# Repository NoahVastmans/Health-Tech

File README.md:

# 🎾 SmartServe Ball — Intelligent Motion Guidance and Apex Detection

## 📘 Project Overview

The **SmartServe Ball** project combines embedded sensing, wireless communication, and data analysis to accurately detect and predict the **apex** of a tennis ball’s trajectory during a throw or serve.

Using a **Seeed XIAO BLE Sense** microcontroller with a **6-axis IMU (LSM6DS3)**, the system identifies:
- The **start of free fall**
- The **apex (highest point)** of the throw
- The **catch or impact moment**
- And transmits timing data via **Bluetooth Low Energy (BLE)**

The goal is to provide **real-time motion insight** for sports technology, validation through **video tracking**, and a foundation for further embedded motion analytics.

---

## 📁 Repository Structure

### 🧠 `Arduino Scripts/`
Contains all embedded code for the SmartServe Ball, including:
- **Apex detection**, **free-fall**, and **BLE telemetry algorithms**
- Modified **`LSM6DS3.cpp`** file required for stable IMU communication  
  *(instructions are detailed in the script-specific README inside this folder)*

Each Arduino script is fully documented in-code.

---

### ⚡ `Electrical Circuit/`
Includes the electrical design and assembly details:
- **KiCad project files** for the wiring and sensor connections  
- **Photos** of the final sensor assembly

> 💡 The PCB was **not fully designed** in CAD — instead, an **adaptable PCB prototyping board** was used.  
> This allowed greater flexibility for multi-layer connections and double-sided component placement.

---

### 🧱 `Prototype Sensor Case/`
3D design files for the **protective casing** used to house the electronics inside a **tennis ball**.  
The case ensures durability while maintaining balance and minimal aerodynamic impact.

---

### 🎥 `Video Tracking/`
Contains:
- The **validation videos** used to visually confirm the apex timing  
- **Video tracking scripts** for extracting apex frames and timestamps  
- A **comparison file** matching BLE-detected and predicted times to the visual apex times

This folder provides the link between **experimental results** and **sensor-based detection accuracy**.

---

### 📹 `Explanation Video/`
A short **demonstration video** summarizing the SmartServe Ball project — explaining the concept and system design in a clear visual format.

---

### 🖥️ `Presentation/`
Contains the **final project presentation slides**, summarizing:
- Motivation and goals  
- Technical design (hardware + software)  
- Validation results and future improvements  

---

### 📄 `Scientific Paper/`
Includes a **concise research-style paper** presenting:
- The experimental setup  
- Measured results  
- Comparison between prediction and detection  
- Relevant literature and references  

---

### 🕰️ `Legacy/`
Contains earlier versions of scripts and design assets intended for future development.  
A separate README inside this folder explains each file’s purpose and how to build upon it.

---

## 🧩 Summary

| Component | Description |
|------------|--------------|
| **Embedded Code** | Apex detection, prediction, BLE telemetry |
| **Electronics** | IMU wiring and modular circuit design |
| **Mechanical Design** | 3D CAD for protective case |
| **Validation** | Video-based apex verification |
| **Demonstration** | Project explanation video |
| **Documentation** | Presentation slides and scientific paper |
| **Legacy Work** | Early-stage materials for continuation |

---

## 🔬 Purpose

The SmartServe Ball demonstrates how **low-power embedded sensing** and **motion algorithms** can yield **accurate trajectory analytics** for sports applications.  
It combines open hardware, transparent validation, and modular design to serve as a **research and development platform** for motion-based performance tracking.

---

## 🧾 License

This repository is open for **educational and research use**.  
Please credit the **SmartServe Ball Project** when reusing or modifying any material.

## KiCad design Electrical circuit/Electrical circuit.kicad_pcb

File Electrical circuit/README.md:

# ⚡ SmartServe Ball — Electrical Circuit

## 📘 Overview

This folder contains all **electrical design resources** for the SmartServe Ball project.  
The system connects a **Seeed XIAO BLE Sense** microcontroller to a **buzzer** and other peripheral components.

---

## 🧩 Contents

| Item | Description |
|------|--------------|
| `SmartServeBall.kicad_sch` | Main circuit schematic showing all connections between the XIAO BLE Sense, IMU, and buzzer |
| `SmartServeBall.kicad_pro` | KiCad project configuration file |
| `Seeeduino XIAO KICAD/` | KiCad symbol and footprint files for Seeed components (used in the schematic) |
| `Assembly Photos/` | Images of the final sensor assembly and adaptable PCB setup |

---

## 🧠 Design Notes

- Only the **schematic** was designed digitally in KiCad.  
- The **PCB itself was not routed** in KiCad or fabricated.

Instead, an **adaptable prototyping PCB** was used for greater flexibility:
- Components were mounted on **both sides** of the board.  
- Components were mounted on top of each other to save space.  
- This approach allowed **rapid iteration** and **easy modification** during testing and validation.

---

## 🔌 Connection Overview

The schematic illustrates: 
- **Power lines** (`3.3V` and `GND`) shared between all components  
- **Digital output pin (D5)** used to drive the **buzzer** for apex and event feedback

---

## 🧰 Tools

- **KiCad 7.x or later** (for viewing and editing schematic files)  
- **Seeeduino XIAO KICAD Library** (included in this folder)

To open the schematic correctly:
1. Ensure the `Seeeduino XIAO KICAD/` folder is in the same directory as the `.kicad_pro` file.  
2. Open `SmartServeBall.kicad_pro` in KiCad.  
3. Verify that component symbols and footprints load without errors.

---

## 🧱 Assembly Process

The assembly was performed in several structured steps to create a compact and robust sensor module:

1. **Top Layer Soldering:**  
   The first layer of components was soldered on the **upper side** of the adaptable PCB.  
   This included the **buzzer**, **resistor**, and **pin extensions** for the Seeed XIAO BLE Sense.

2. **Power Wiring:**  
   Next, the **power supply wires** were soldered to the corresponding **3.3V** and **GND** pins, ensuring solid electrical contact and mechanical stability.

3. **Base Layer Protection:**  
   After soldering the lower connections, a **thin layer of hot glue** was applied to the **bottom side** of the PCB to insulate and protect the solder joints.

4. **Battery Holder Placement:**  
   The **battery holder** was then positioned directly on top of the glued surface, forming the **second hardware layer** of the design.

5. **Final Power Connection:**  
   Finally, the **power wires** were soldered to the **battery holder terminals**, completing the electrical circuit and enabling portable operation.

This stacked-layer assembly provided an **efficient use of space** and **robust wiring**, allowing the electronics to fit neatly inside the SmartServe Ball’s protective enclosure.

---

## 📷 Assembly

The `Assembly_Photos/` folder shows:
- The **adaptable PCB layout**  
- The **component placement** on both board sides  

These images serve as a **reference for replication or redesign**.

---

## 🧾 License

These files are shared for **educational and research purposes** under the SmartServe Ball project.  
Please credit the **SmartServe Ball Team** when reusing or adapting the schematic or library components.

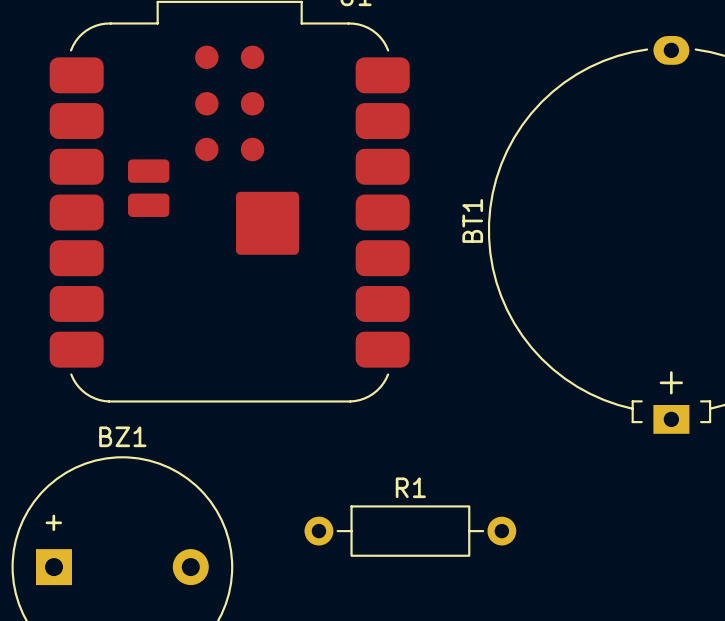
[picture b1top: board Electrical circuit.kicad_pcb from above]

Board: 2 copper layers, 4 parts (0 on the bottom side), 4 nets, no tracks yet.

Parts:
BT1: Battery_Cell; Battery_Panasonic_CR2032-HFN_Horizontal_CircularHoles
BZ1: Buzzer; Buzzer_12x9.5RM7.6
R1: 33 Ohm; R_Axial_DIN0207_L6.3mm_D2.5mm_P10.16mm_Horizontal
U1: SeeeduinoXIAO; MCU_Seeed_ESP32C3

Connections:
GND: BT1.2 (-), R1.2, U1.13 (GND)
unnamed: BT1.1 (+), U1.12 (3V3)
unnamed: BZ1.1 (+), U1.5 (PA8_A4_D4_SDA)
unnamed: BZ1.2 (-), R1.1

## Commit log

2025-09-10 Attempt to store data on flash memory
2025-09-17 Create FindingVelocity
    Code to find velocity from ACC data
2025-09-18 New Arduino scripts
    For buzzer testing, storing on ram and streaming through bluetooth
2025-09-18 rename directory and files
2025-09-21 Add flight detection for Seeed Sensor
    flight detection model for a tenis ball based on acceleration, speed and orientation. Free fall detection from seed sensor and basic low pass filter. Then AHRS model for orientation
2025-09-21 Add MadgwickAHRS header file for IMU algorithms
    edit to public quaternion values
2025-09-21 Implement LSM6DS3 driver for Arduino
    mute line 108, is not necessary for current implementation mbed imu
2025-09-21 Add LSM6DS3 driver implementation
    mute line 108 and 110 not necessary for current implementation
2025-09-22 buzzer pin change
2025-09-23 Pin update
2025-09-27 Fix bluetooth
2025-09-27 Update the detecting apex with combined velocity file
2025-09-28 Edit flight detection logic and pin configuration
    clean structure. adjustments for flight detection and pin configuration. Print for debugging
2025-09-28 Improve debug output in flight detection script
    Refined debug output for clarity in flight detection.
2025-10-05 fix calibration frecuency data and debugging
2025-10-06 debugging
2025-10-07 With free fall detection
2025-10-07 Cleaning the code
2025-10-07 Apex_prediction
2025-10-07 Cleaning code
2025-10-07 Using threshold in stead of freefall detection
2025-10-09 adapt freefall detection
2025-10-09 debugging prediction
2025-10-09 tone update
2025-10-09 Prediction in this code
2025-10-09 Restoring good code + cleaning code
2025-10-11 Github Cleaning
    Rename important files
    Document important code
    Archive old files
2025-10-11 add readme
2025-10-11 Electrical circuit desing added
2025-10-12 Video Tracking
2025-10-12 Uploaded video tracking code
2025-10-12 Create Videotracking
2025-10-12 Serial version
2025-10-12 Reorganise videotracking
2025-10-12 Gifs + results added
2025-10-13 Rename
2025-10-13 Name change
2025-10-13 Pictures sensor
2025-10-13 Video
2025-10-13 Reorganise
2025-10-13 Delete Prototype Sensor Case/sensor case_left.SLDPRT
    na
2025-10-13 Delete Prototype Sensor Case/sensor case_right.SLDPRT
    na
2025-10-13 rearange AHRS
2025-10-13 Add README.md with initial content
2025-10-13 Update README with project description
    Added description for the Prototype Sensor Case.
2025-10-13 Enhance README with project details and guidelines for use of CAD files
    Updated README.md to include detailed project information, contents, design notes, implementation overview, tools, and licensing for the CAD files use
2025-10-13 Fix quaternion rotation calculations for acceleration
2025-10-13 Update config_free_fall_detect function header
    Refactor free fall detection function header for clarity.
2025-10-13 Enhance README with project details and instructions for legacy scripts
    Added comprehensive documentation for the SmartServe Ball project, including setup prerequisites, hardware and software requirements, algorithm summary, and usage steps.
2025-10-13 Simplify buzzer beep scheduling in Apex Detection
    Removed delay compensation from buzzer beep scheduling.
2025-10-14 Correct filename
2025-10-14 Paper
2025-10-14 Presentation
2025-10-15 Last versions
2025-10-16 Provide pptx
2025-10-16 include graphs
